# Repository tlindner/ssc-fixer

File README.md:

# ssc-fixer

A cartridge-port interposer that keeps the Tandy **Speech/Sound Cartridge**'s PIC 7040
MCU and AY-3-8913 PSG at 1.79 MHz when a CoCo runs at double speed. Without it, both
run at 3.58 MHz, which makes the firmware run twice as fast and the music play an
octave higher. The cartridge itself is not modified.

There are three designs:

* **Rev A, [DESIGN.md](DESIGN.md):** substitutes Q, with 3 chips plus an oscillator. It handles CoCo E of
  0.89 and 1.79 MHz, including mixed-speed operation. Simulation: [sim/ssc_fixer_sim.py](sim/ssc_fixer_sim.py)
* **Rev B, [DESIGN-4MHz.md](DESIGN-4MHz.md):** a bus bridge built from 17 74HCT chips plus an oscillator.
  It handles any CoCo E up to 4 MHz by giving the SSC its own stock-speed private bus, which also runs
  the −5 V converter at its stock frequency. Simulation: [sim/bridge_sim.py](sim/bridge_sim.py)
* **Rev C, [DESIGN-revC.md](DESIGN-revC.md):** rev A's job (0.89 and 1.79 MHz) done in a single ATF16V8B
  GAL plus an oscillator, with a more symmetric clock. GAL source: [revc/sscfixc.pld](revc/sscfixc.pld).
  Simulation: [sim/revc_sim.py](sim/revc_sim.py), which reads the equations from the `.pld`.

The schematic references are to pages 17–18 of the Speech/Sound Cartridge service
manual, which is not included here for copyright reasons. Copies are available from
CoCo archive sites.

Status: design only. No hardware has been built or tested yet.

## License

MIT. See [LICENSE](LICENSE).

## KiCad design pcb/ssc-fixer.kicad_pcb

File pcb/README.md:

# Rev A PCB

KiCad 10 board for the rev A interposer in [DESIGN.md](../DESIGN.md).
[gen_pcb.py](gen_pcb.py) generates the board from scratch: outline, footprints, nets, routing and GND pour.

```
/Applications/KiCad/KiCad.app/Contents/Frameworks/Python.framework/Versions/Current/bin/python3 pcb/gen_pcb.py
/Applications/KiCad/KiCad.app/Contents/MacOS/kicad-cli pcb drc --severity-all pcb/ssc-fixer.kicad_pcb
```

DRC result: 0 violations, 0 unconnected items.

## Layout

* **J1**: 40 gold fingers at 0.1" pitch on a 53.3 mm (2.1") tab. Odd pins are on the top (F.Cu) and even pins on the bottom, with pin 1 at the left when you look at the top.
* **J2**: a 2x20 0.1" through-hole card-edge socket. J2-n sits directly above J1-n.
* **Pass-through:** each odd pin has its own trace on F.Cu and each even pin has one on B.Cu. Pins 8–40 squeeze into a 0.6 mm bus on the right, which leaves a parts window in the middle of the board.
* **Logic:** in that window. It taps E (pin 6) and +5 V (pin 9) from their traces, takes Q straight from finger J1-7 and drives J2-7 through R1. GND comes from J2-34 over the top of the socket. The board has a GND pour on both layers.
* The script's small grid maze router does the logic routing.

## Changes from DESIGN.md

* **SMD logic instead of DIP:** U1–U3 are SOIC-14, X1 is a 5×3.2 mm 4-pin SMD oscillator (pin 1 = enable, tied high), and R/C are 0805 (C5 is 1206). Through-hole pins would collide with the pass-through traces.
* **No schematic:** the nets are assigned directly in the PCB and follow the DESIGN.md netlist.

## Check before ordering

1. **Finger side and pin 1.** The board assumes odd CoCo pins are on the component side, with pin 1 at the left. Pass-through pins map 1:1 whichever way round this is, but if the assumption is wrong, the logic taps the wrong fingers for E, Q and +5 V.
2. **The J2 footprint is a placeholder:** 2.54 mm pitch, 5.08 mm (0.2") between rows, 1.0 mm drill. Match it to the socket you buy. A through-hole socket also makes the SSC stand at right angles to this board. Check that this fits the CoCo or Multi-Pak.
3. **Finger length and tab width** (8 mm, 53.3 mm). Check them against the CoCo connector. Order hard gold and a 20–45° bevel.

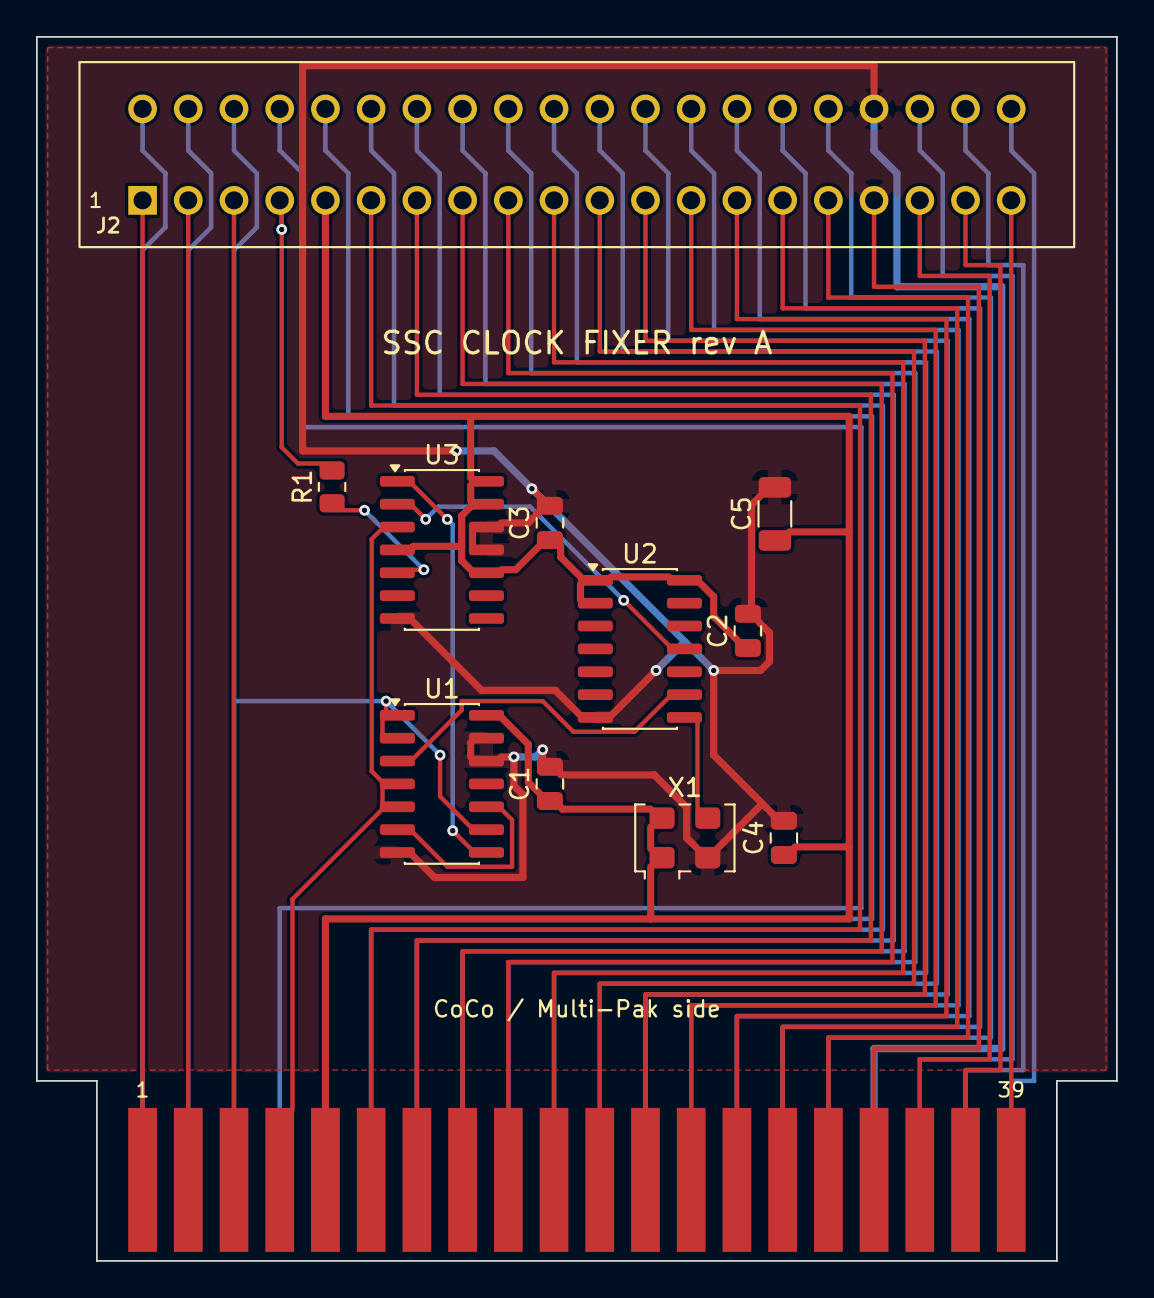
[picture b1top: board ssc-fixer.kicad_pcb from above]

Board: 2 copper layers, 60.0 x 68.0 mm, 12 parts (0 on the bottom side), 46 nets.

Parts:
C1, C2, C3, C4: 100n; C_0805_2012Metric
C5: 10u; C_1206_3216Metric
J1: CoCo cartridge edge 2x20 P2.54; CoCo_Edge_2x20_P2.54mm
J2: 40-pin 0.1in card-edge socket, rows 0.2in; CardEdge_Socket_2x20_P2.54mm_Row5.08mm
R1: 47; R_0805_2012Metric
U1: 74HCT00; SOIC-14_3.9x8.7mm_P1.27mm
U2: 74HC164; SOIC-14_3.9x8.7mm_P1.27mm
U3: 74HCT74; SOIC-14_3.9x8.7mm_P1.27mm
X1: 28.63636MHz; Oscillator_SMD_EuroQuartz_XO53-4Pin_5.0x3.2mm

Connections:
+5V: C1.1, C2.1, C3.1, C4.1, C5.1, J1.9, J2.9, U1.14, U2.1, U2.2, U2.14, U3.4, U3.10, U3.13, U3.14, X1.1, X1.4
+12V: J1.2, J2.2
-12V: J1.1, J2.1
/E: U1.3, U2.9
/Q: U1.6, U1.10
A0: J1.19, J2.19
A1: J1.20, J2.20
A2: J1.21, J2.21
A3: J1.22, J2.22
A4: J1.23, J2.23
A5: J1.24, J2.24
A6: J1.25, J2.25
A7: J1.26, J2.26
A8: J1.27, J2.27
A9: J1.28, J2.28
A10: J1.29, J2.29
A11: J1.30, J2.30
A12: J1.31, J2.31
A13: J1.37, J2.37
A14: J1.38, J2.38
A15: J1.39, J2.39
CART: J1.8, J2.8
CLRn: U1.8, U3.1
CTS: J1.32, J2.32
D0: J1.10, J2.10
D1: J1.11, J2.11
D2: J1.12, J2.12
D3: J1.13, J2.13
D4: J1.14, J2.14
D5: J1.15, J2.15
D6: J1.16, J2.16
D7: J1.17, J2.17
E: J1.6, J2.6, U1.1, U1.2, U1.9
GND: C1.2, C2.2, C3.2, C4.2, C5.2, J1.33, J1.34, J2.33, J2.34, U1.7, U1.12, U1.13, U2.7, U3.7, U3.11, U3.12, X1.2
HALT: J1.3, J2.3
NMI: J1.4, J2.4
OSC: U2.8, X1.3
QX: J2.7, R1.2
QX_INT: R1.1, U3.5
Q_COCO: J1.7, U1.4, U1.5, U3.3
R/W: J1.18, J2.18
RESET: J1.5, J2.5
SCS: J1.36, J2.36
SLENB: J1.40, J2.40
SND: J1.35, J2.35
T200: U2.11, U3.2
